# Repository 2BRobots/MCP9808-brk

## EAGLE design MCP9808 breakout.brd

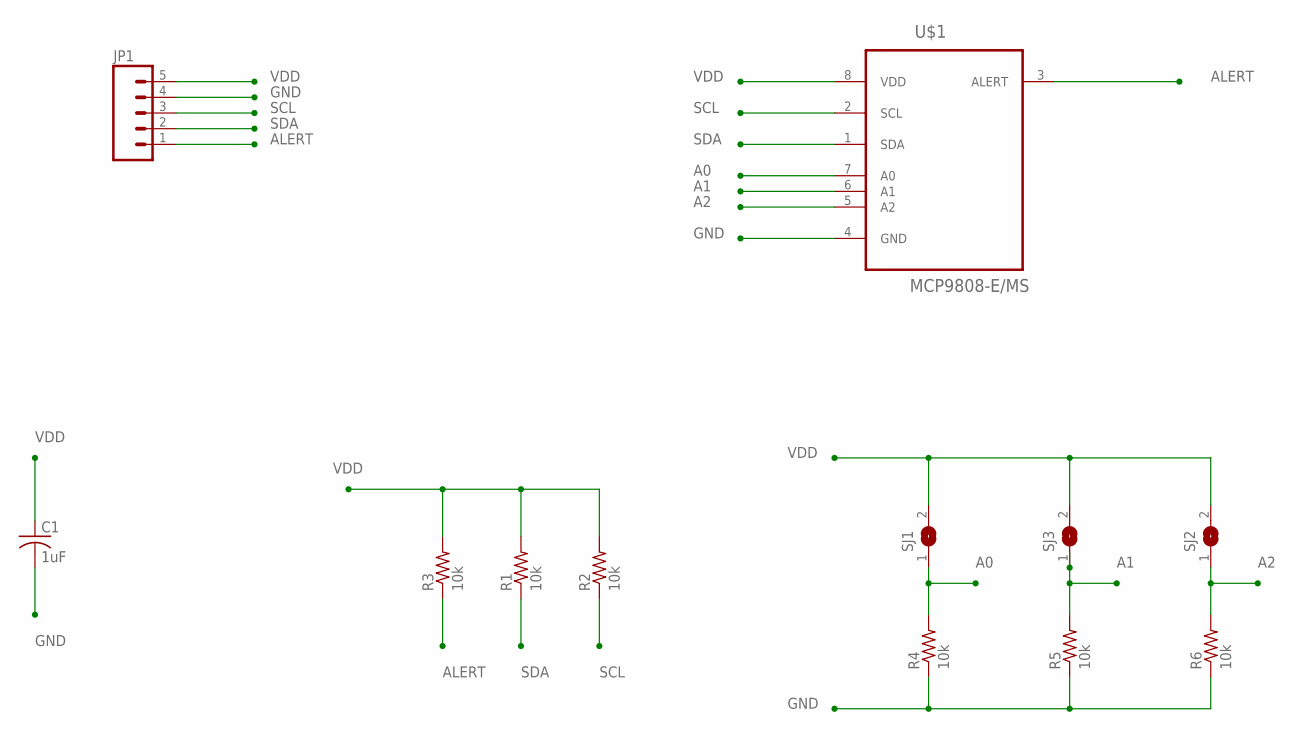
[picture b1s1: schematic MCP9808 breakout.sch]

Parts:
C1: 1uF; C0603K
JP1: M05NO_SILK; 1X05_NO_SILK
R1, R2, R3, R4, R5, R6: 10k; R0805
SJ1, SJ2, SJ3: SJ
U$1: MCP9808-E/MS; SOP65P490X110-8N

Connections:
A0: R4.2, SJ1.1, U$1.7 (A0)
A1: R5.2, SJ3.1, U$1.6 (A1)
A2: R6.2, SJ2.1, U$1.5 (A2)
ALERT: JP1.1, R3.1, U$1.3 (ALERT)
GND: C1.2, JP1.4, R4.1, R5.1, R6.1, U$1.4 (GND)
SCL: JP1.3, R2.1, U$1.2 (SCL)
SDA: JP1.2, R1.1, U$1.1 (SDA)
VDD: C1.1, JP1.5, R1.2, R2.2, R3.2, SJ1.2, SJ2.2, SJ3.2, U$1.8 (VDD)

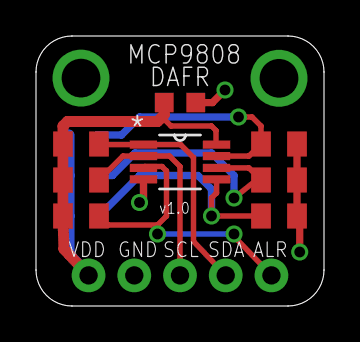
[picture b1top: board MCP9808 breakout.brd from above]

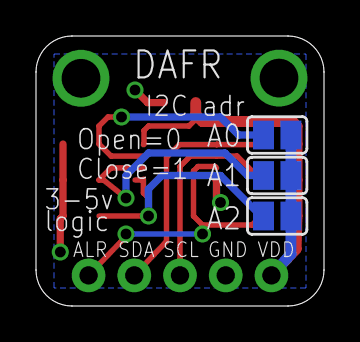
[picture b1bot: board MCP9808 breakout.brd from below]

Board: 2 copper layers, 16.0 x 15.0 mm, 12 parts (3 on the bottom side), 8 nets.

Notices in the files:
parts and their libraries:
SparkFun-Connectors: Licensing: Creative Commons ShareAlike 4.0 International - https://creativecommons.org/licenses/by-sa/4.0
